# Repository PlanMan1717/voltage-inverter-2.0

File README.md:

# voltage-inverter-2.0
An untested voltage inverter

> THIS IS AN UNTESTED DESIGN. I am not responsible for anything.

## License?
CC BY-SA 4.0

Made with KiCad;
https://kicad-pcb.org/

Simulated with CircuitJS;
https://www.falstad.com/circuit/circuitjs.html Source in "sim.circuitjs.txt"

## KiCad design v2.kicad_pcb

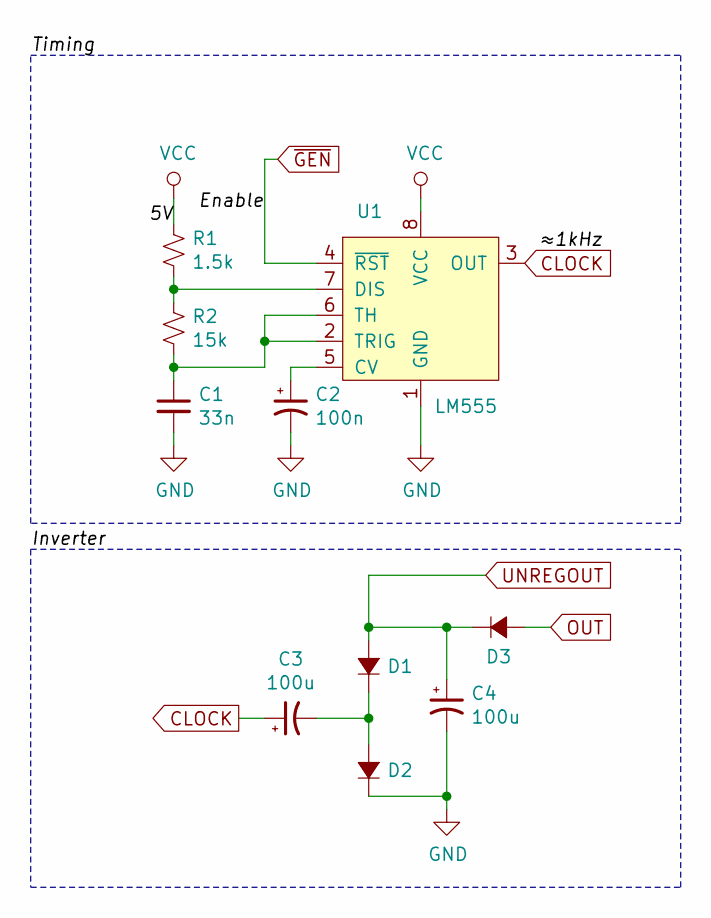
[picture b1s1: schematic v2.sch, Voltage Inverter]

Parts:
C1: 33n; C_1210_3225Metric_Pad1.42x2.65mm_HandSolder
C2: 100n; C_1812_4532Metric_Pad1.30x3.40mm_HandSolder
C3, C4: 100u; CP_Elec_5x5.9
D1, D2, D3: D_SOD-123F
R1: 1.5k; R_1206_3216Metric_Pad1.42x1.75mm_HandSolder
R2: 15k; R_1806_4516Metric_Pad1.57x1.80mm_HandSolder
U1: LM555; SSOP-8_5.25x5.24mm_P1.27mm

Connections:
CLOCK: C3.1, U1.3 (OUT)
GND: C1.2, C2.2, C4.2, D2.1 (K), U1.1 (GND)
unnamed: C1.1, R2.2, U1.2 (TRIG), U1.6 (TH)
unnamed: C2.1, U1.5 (CV)
unnamed: C3.2, D1.1 (K), D2.2 (A)
unnamed: R1.2, R2.1, U1.7 (DIS)
OUT: D3.2 (A)
UNREGOUT: C4.1, D1.2 (A), D3.1 (K)
VCC: R1.1, U1.8 (VCC)
~GEN: U1.4 (~RST)

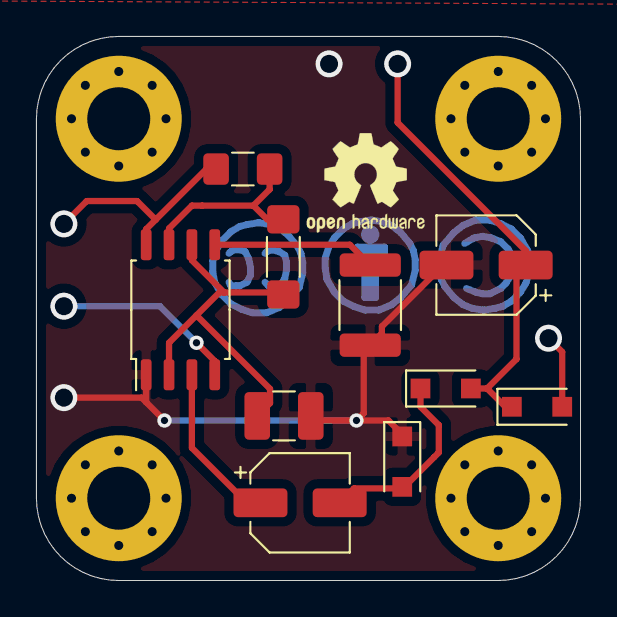
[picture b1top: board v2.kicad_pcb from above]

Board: 2 copper layers, 30.2 x 30.2 mm, 10 parts (0 on the bottom side), 8 nets.

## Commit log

2020-05-09 Create license.txt
    CC BY-SA 4.0
2020-05-09 Create sim.circuitjs.txt
    Open with CircuitJS: https://www.falstad.com/circuit/circuitjs.html

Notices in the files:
v2.sch:
creativecommons.org/licenses/by-sa/4.0
Released under Creative Commons BY-SA 4.0
